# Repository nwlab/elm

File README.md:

# Elm Project

Emergency Lighting Module

This module handles the emergency lighting system for the Elm project, ensuring proper illumination during power outages and other emergency situations.

## Features
- Automatic activation during power outages
- Battery status monitoring
- Manual override for testing and maintenance

## Usage
Import the module and initialize the emergency lighting system in your Elm project. The system will automatically manage the lights based on power availability and emergency conditions.

## Modules

Based on Bq25606 battery management IC for handling power and battery status in the emergency lighting system.

### Bq25606 Module
- Monitors battery voltage and current
- Controls charging and discharging of the battery
- Provides status information to the emergency lighting system

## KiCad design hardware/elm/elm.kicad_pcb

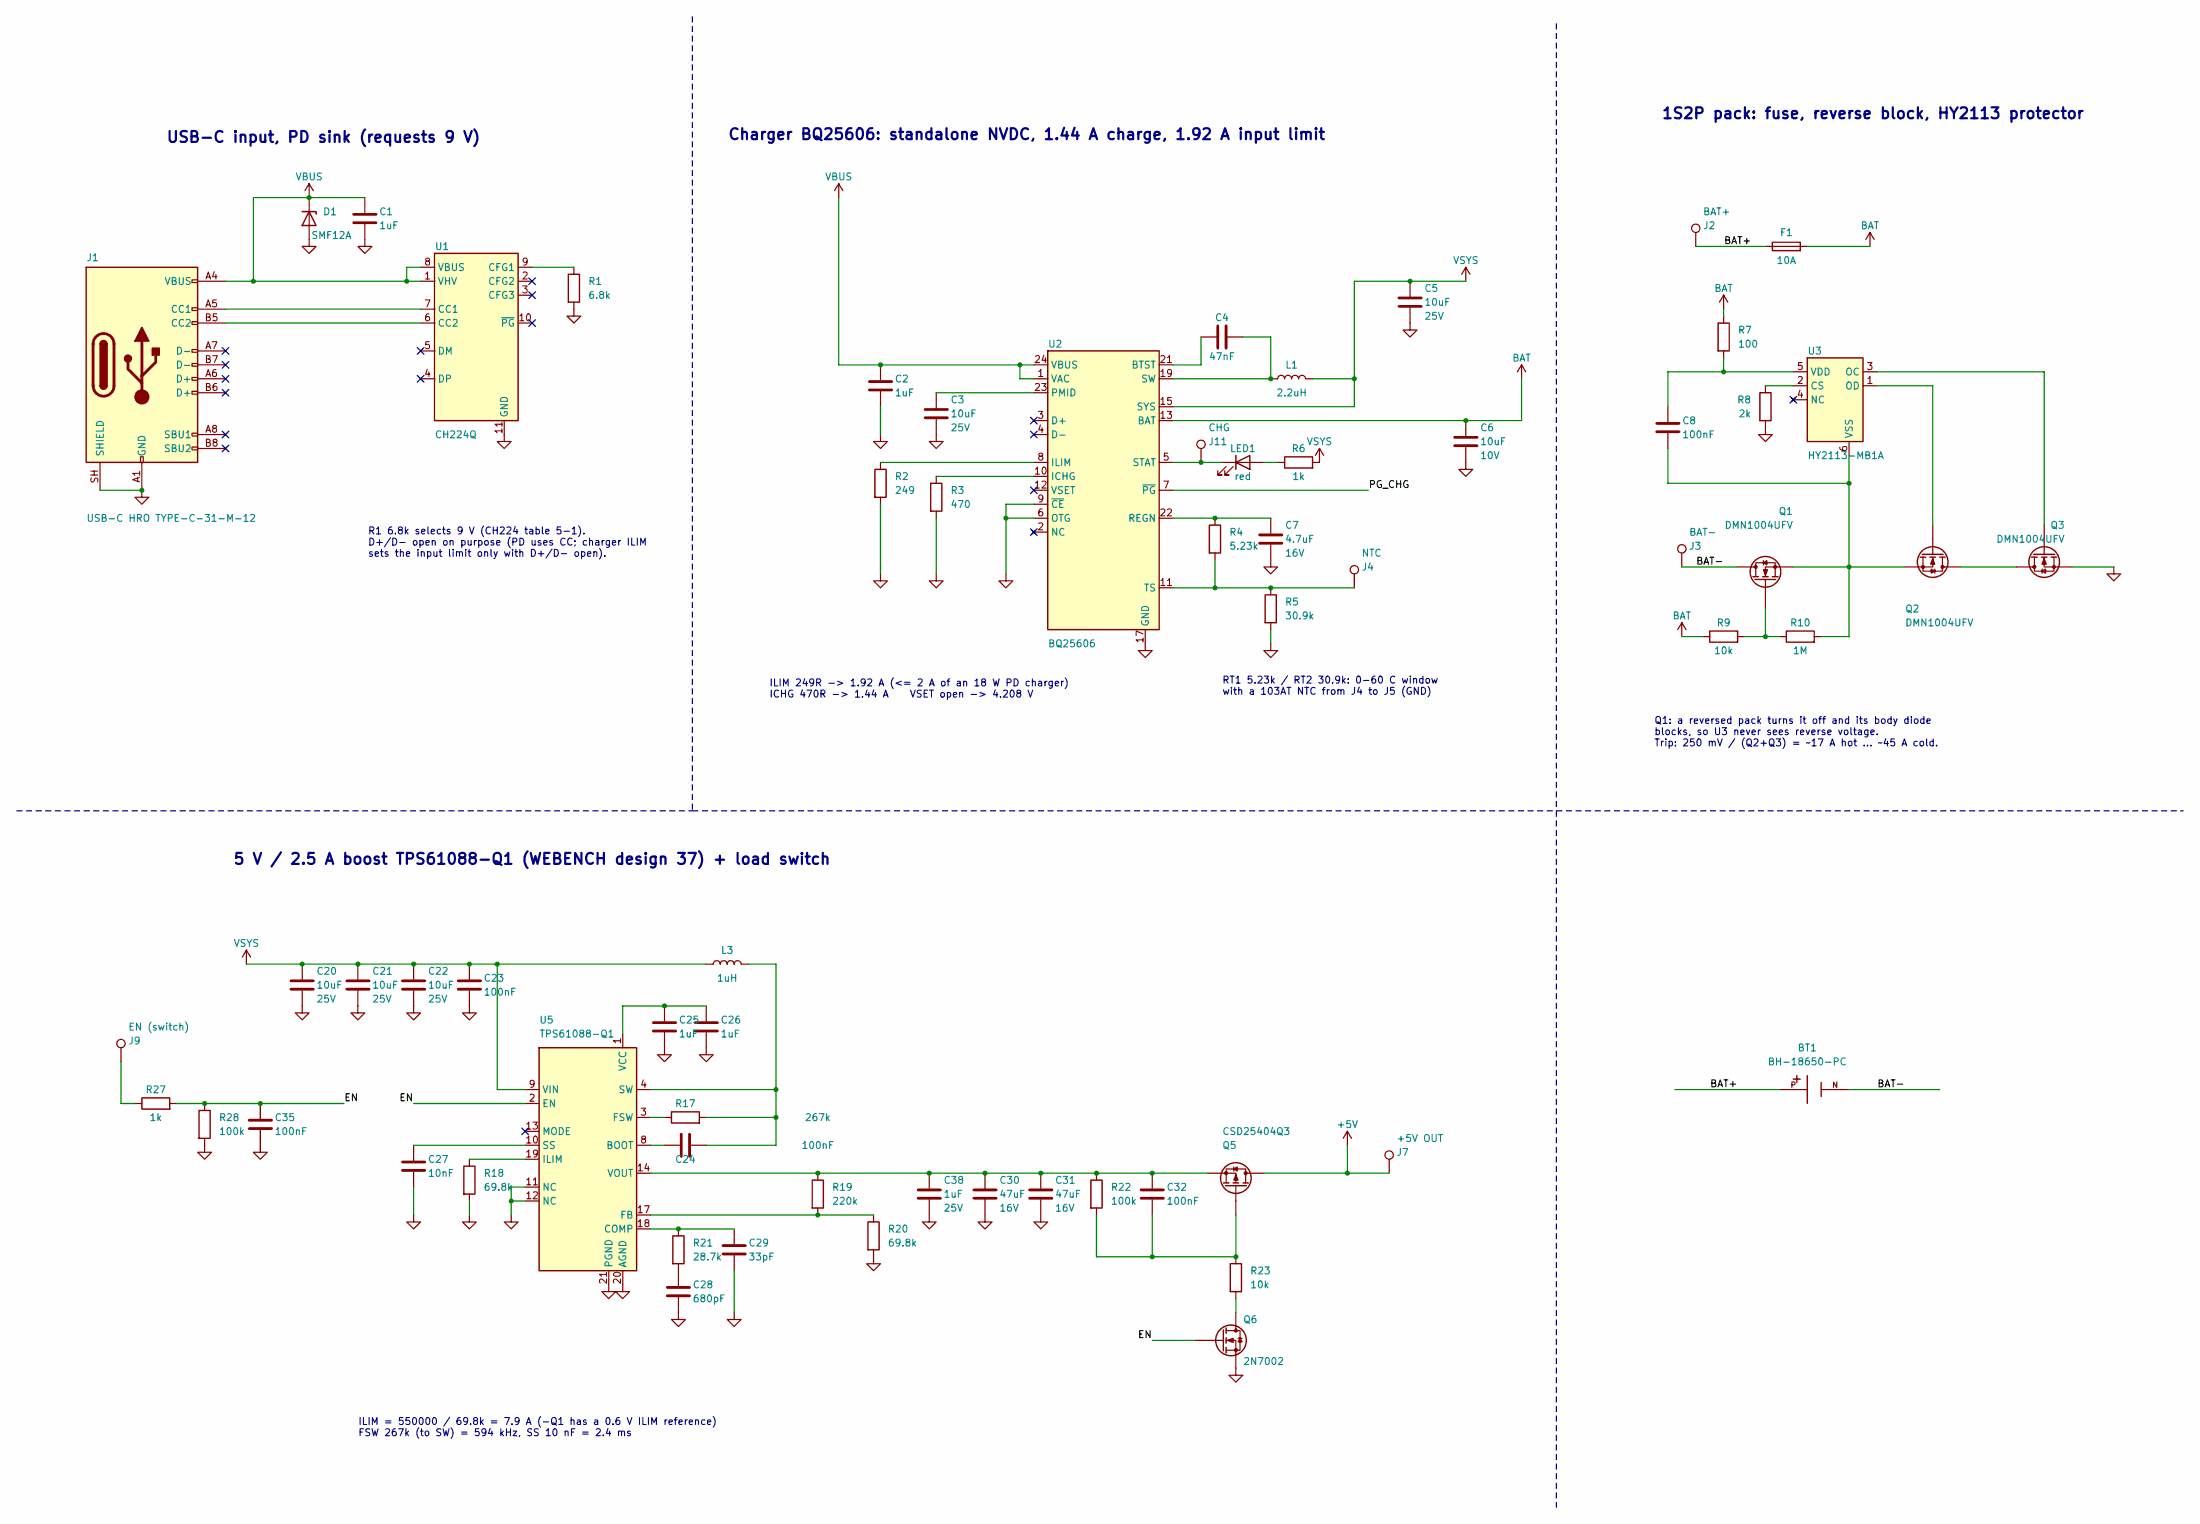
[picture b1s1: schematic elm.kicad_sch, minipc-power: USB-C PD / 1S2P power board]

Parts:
BT1: BH-18650-PC; BatteryHolder_MPD_BH-18650-PC; PARTREV 05/17/19
C1, C2, C25, C26: 1uF; C_0603_1608Metric; LCSC C15849
C3, C5, C20, C21, C22: 10uF; C_0805_2012Metric; Voltage 25V; LCSC C15850
C4: 47nF; C_0402_1005Metric; LCSC C307434
C6: 10uF; C_0603_1608Metric; Voltage 10V; LCSC C19702
C7: 4.7uF; C_0603_1608Metric; Voltage 16V; LCSC C19666
C8, C23, C24, C32, C35: 100nF; C_0402_1005Metric; LCSC C1525
C27: 10nF; C_0402_1005Metric; LCSC C15195
C28: 680pF; C_0402_1005Metric; LCSC C307451
C29: 33pF; C_0402_1005Metric; LCSC C70465
C30, C31: 47uF; C_1210_3225Metric; Voltage 16V; LCSC C77101
C38: 1uF; C_0402_1005Metric; Voltage 25V; LCSC C52923
D1: SMF12A; D_SOD-123F; LCSC C123800
F1: 10A; Fuse_Littelfuse-NANO2-451_453; LCSC C44479
J1: USB-C HRO TYPE-C-31-M-12; USB_C_Receptacle_HRO_TYPE-C-31-M-12; LCSC C165948
J2: BAT+; TestPoint_THTPad_2.5x2.5mm_Drill1.2mm
J3: BAT-; TestPoint_THTPad_D2.5mm_Drill1.2mm
J4: NTC; TestPoint_THTPad_2.0x2.0mm_Drill1.0mm
J7: +5V OUT; TestPoint_THTPad_2.5x2.5mm_Drill1.2mm
J9: EN (switch); TestPoint_THTPad_2.0x2.0mm_Drill1.0mm
J11: CHG; TestPoint_THTPad_2.0x2.0mm_Drill1.0mm
L1: 2.2uH; FXL0630-2R2-M; LCSC C167218
L3: 1uH; FXL0630-1R0-M; LCSC C167216
LED1: red; LED_0603_1608Metric; LCSC C2286
Q1, Q2, Q3: DMN1004UFV; Diodes_PowerDI3333-8; LCSC C316138
Q5: CSD25404Q3; VSON-8_3.3x3.3mm_P0.65mm_NexFET; LCSC C2865523
Q6: 2N7002; SOT-23; LCSC C8545
R1: 6.8k; R_0402_1005Metric; LCSC C25917
R2: 249; R_0402_1005Metric; LCSC C25096
R3: 470; R_0402_1005Metric; LCSC C25117
R4: 5.23k; R_0402_1005Metric; LCSC C25907
R5: 30.9k; R_0402_1005Metric; LCSC C270615
R6, R27: 1k; R_0402_1005Metric; LCSC C11702
R7: 100; R_0402_1005Metric; LCSC C25076
R8: 2k; R_0402_1005Metric; LCSC C4109
R9, R23: 10k; R_0402_1005Metric; LCSC C25744
R10: 1M; R_0402_1005Metric; LCSC C26083
R17: 267k; R_0402_1005Metric; LCSC C270622
R18, R20: 69.8k; R_0402_1005Metric; LCSC C26985
R19: 220k; R_0402_1005Metric; LCSC C25767
R21: 28.7k; R_0402_1005Metric; LCSC C26972
R22, R28: 100k; R_0402_1005Metric; LCSC C25741
U1: CH224Q; CH224Q_C46061833; LCSC C46061833
U2: BQ25606; Texas_RGE0024H_VQFN-24-1EP_4x4mm_P0.5mm_EP2.7x2.7mm_Thermal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; LCSC C374063
U3: HY2113-MB1A; SOT-23-6; LCSC C168772
U5: TPS61088-Q1; Texas_VQFN-RHL-20_ThermalVias; LCSC C1850341

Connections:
+5V: J7.1 (1_1), Q5.1 (D), Q5.2 (D), Q5.3 (D)
/BAT+: BT1.P, F1.1, J2.1 (1_1)
/BAT-: BT1.N, J3.1 (1_1), Q1.5 (D)
/EN: C35.1, Q6.1 (G), R27.2, R28.1, U5.2 (EN)
/PG_CHG: U2.7 (~PG)
BAT: C6.1, F1.2, R7.1, R9.1, U2.13 (BAT), U2.14 (BAT)
GND: C1.2, C2.2, C3.2, C5.2, C6.2, C7.2, C20.2, C21.2, C22.2, C23.2, C25.2, C26.2, C27.2, C28.2, C29.2, C30.2, C31.2, C35.2, C38.2, D1.2 (A), J1.A1 (GND), J1.A12 (GND), J1.B1 (GND), J1.B12 (GND), J1.SH (SHIELD), Q3.1 (S), Q3.2 (S), Q3.3 (S), Q6.2 (S), R1.2, R2.2, R3.2, R5.2, R8.2, R18.2, R20.2, R28.2, U1.11 (GND), U2.6 (OTG), U2.9 (~CE), U2.17 (GND), U2.18 (GND), U2.25 (GND), U5.11 (NC), U5.12 (NC), U5.20 (AGND), U5.21 (PGND)
unnamed: C4.2, L1.1, U2.19 (SW), U2.20 (SW)
unnamed: C24.2, L3.2, R17.2, U5.4 (SW), U5.5 (SW), U5.6 (SW), U5.7 (SW)
unnamed: C28.1, R21.2
unnamed: J1.A5 (CC1), U1.7 (CC1)
unnamed: J1.B5 (CC2), U1.6 (CC2)
unnamed: J9.1 (1_1), R27.1
unnamed: LED1.2 (A), R6.1
unnamed: J11.1 (1_1), LED1.1 (K), U2.5 (STAT)
unnamed: Q1.4 (G), R9.2, R10.1
unnamed: Q2.5 (D), Q3.5 (D)
unnamed: Q2.4 (G), U3.1 (OD)
unnamed: Q3.4 (G), U3.3 (OC)
unnamed: C32.2, Q5.4 (G), R22.2, R23.1
unnamed: C30.1, C31.1, C32.1, C38.1, Q5.5 (S), R19.1, R22.1, U5.14 (VOUT), U5.15 (VOUT), U5.16 (VOUT)
unnamed: Q6.3 (D), R23.2
unnamed: R1.1, U1.9 (CFG1)
unnamed: C4.1, U2.21 (BTST)
unnamed: R3.1, U2.10 (ICHG)
unnamed: R2.1, U2.8 (ILIM)
unnamed: C3.1, U2.23 (PMID)
unnamed: C7.1, R4.1, U2.22 (REGN)
unnamed: J4.1 (1_1), R4.2, R5.1, U2.11 (TS)
unnamed: R8.1, U3.2 (CS)
unnamed: C8.1, R7.2, U3.5 (VDD)
unnamed: C8.2, Q1.1 (S), Q1.2 (S), Q1.3 (S), Q2.1 (S), Q2.2 (S), Q2.3 (S), R10.2, U3.6 (VSS)
unnamed: C24.1, U5.8 (BOOT)
unnamed: C29.1, R21.1, U5.18 (COMP)
unnamed: R19.2, R20.1, U5.17 (FB)
unnamed: R17.1, U5.3 (FSW)
unnamed: R18.1, U5.19 (ILIM)
unnamed: C27.1, U5.10 (SS)
unnamed: C25.1, C26.1, U5.1 (VCC)
VBUS: C1.1, C2.1, D1.1 (K), J1.A4 (VBUS), J1.A9 (VBUS), J1.B4 (VBUS), J1.B9 (VBUS), U1.1 (VHV), U1.8 (VBUS), U2.1 (VAC), U2.24 (VBUS)
VSYS: C5.1, C20.1, C21.1, C22.1, C23.1, L1.2, L3.1, R6.2, U2.15 (SYS), U2.16 (SYS), U5.9 (VIN)

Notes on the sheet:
R1 6.8k selects 9 V (CH224 table 5-1). D+/D- open on purpose (PD uses CC; charger ILIM sets the input limit only with D+/D- open).
ILIM = 550000 / 69.8k = 7.9 A (-Q1 has a 0.6 V ILIM reference) FSW 267k (to SW) = 594 kHz, SS 10 nF = 2.4 ms
Q1: a reversed pack turns it off and its body diode blocks, so U3 never sees reverse voltage. Trip: 250 mV / (Q2+Q3) = ~17 A hot ... ~45 A cold.
ILIM 249R -> 1.92 A (<= 2 A of an 18 W PD charger) ICHG 470R -> 1.44 A VSET open -> 4.208 V
USB-C input, PD sink (requests 9 V)
1S2P pack: fuse, reverse block, HY2113 protector
RT1 5.23k / RT2 30.9k: 0-60 C window with a 103AT NTC from J4 to J5 (GND)
Charger BQ25606: standalone NVDC, 1.44 A charge, 1.92 A input limit
5 V / 2.5 A boost TPS61088-Q1 (WEBENCH design 37) + load switch

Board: 4 copper layers, 64 parts (1 on the bottom side), 40 nets, no tracks yet.
